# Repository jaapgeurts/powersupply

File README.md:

# Variable power supply

This project is my first attempt at a variable voltage power supply with current limiting.

The power supply can regulate from 0-25v and handle about 3 Amps depending on how well the series pass transistor is heatsinked.

Regulation is not very stable when current limiting kicks in. This requires further analysis.

If you've built and/or improved this project I would like to hear from you.

**Warning**

I make no guarantees towards the correctness or quality of this project.

If you decide to build this project and use this power supply, you do so at your own risk.

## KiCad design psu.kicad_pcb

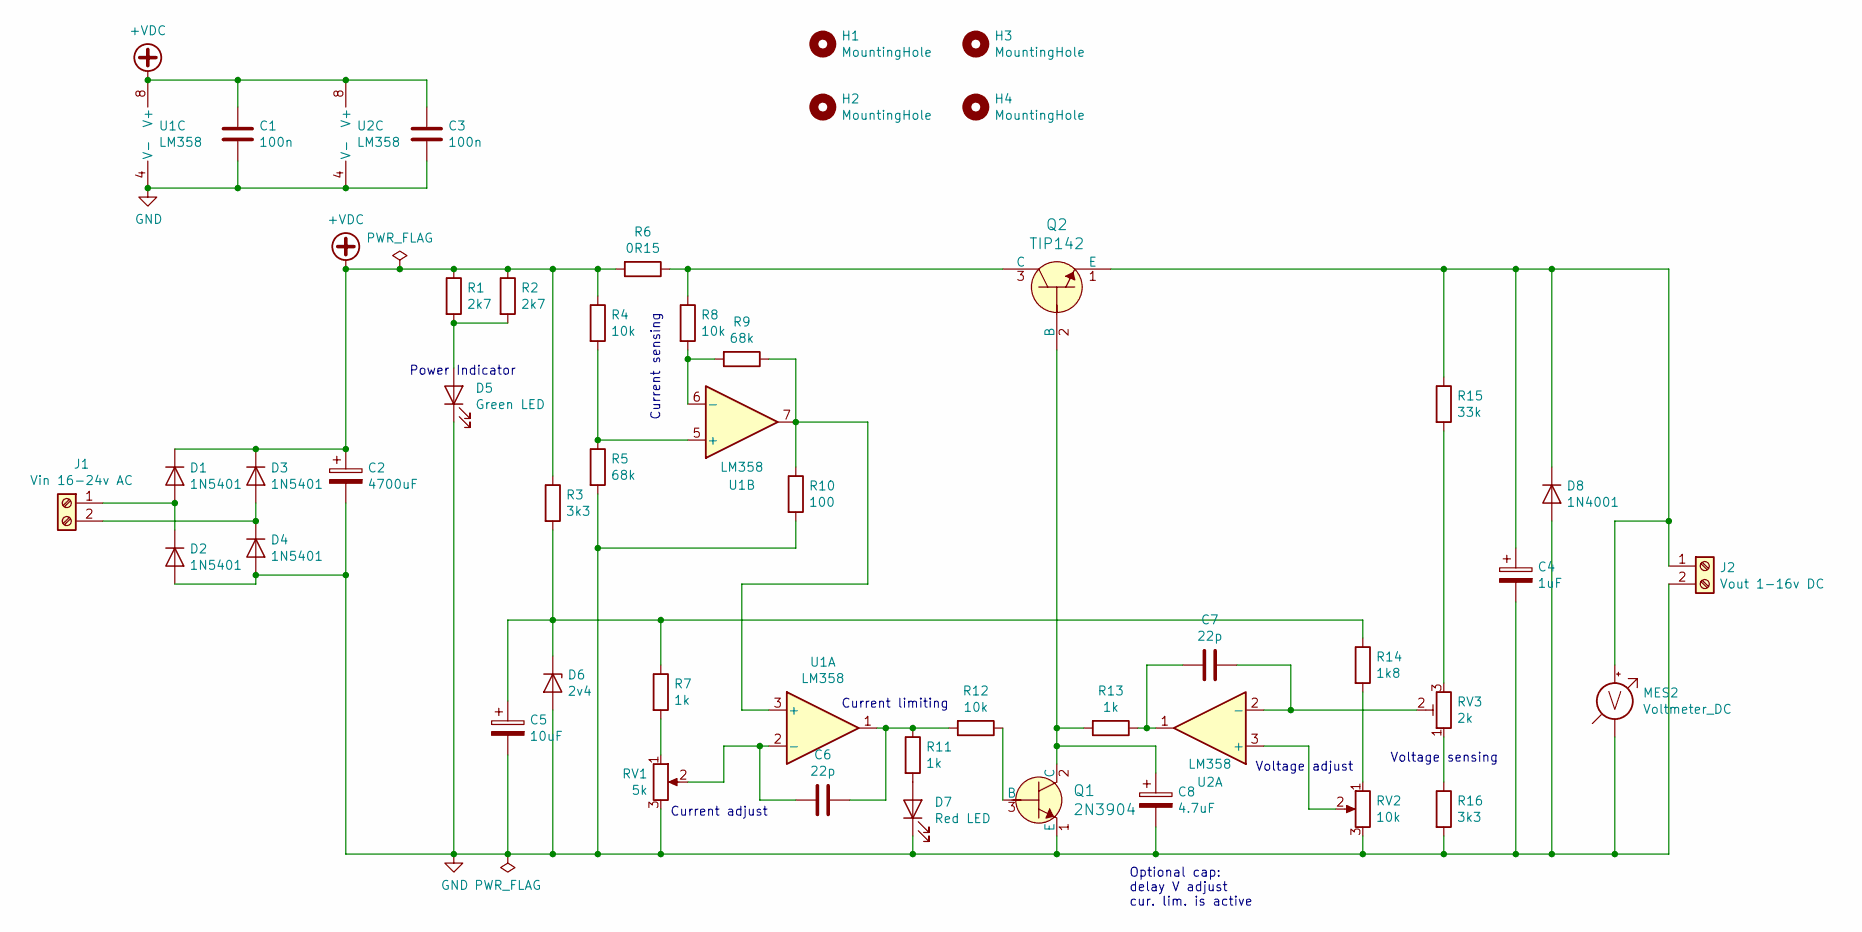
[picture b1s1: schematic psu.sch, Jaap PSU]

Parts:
C1, C3: 100n; C_Disc_D5.1mm_W3.2mm_P5.00mm
C2: 4700uF; CP_Radial_D16.0mm_P7.50mm
C4: 1uF; CP_Radial_D5.0mm_P2.50mm
C5: 10uF; CP_Radial_D5.0mm_P2.50mm
C6, C7: 22p; C_Disc_D5.1mm_W3.2mm_P5.00mm
C8: 4.7uF; CP_Radial_D5.0mm_P2.50mm
D1, D2, D3, D4: 1N5401; D_DO-201AD_P15.24mm_Horizontal
D5: Green LED; PinHeader_1x02_P2.54mm_Vertical
D6: 2v4; D_DO-35_SOD27_P10.16mm_Horizontal
D7: Red LED; PinHeader_1x02_P2.54mm_Vertical
D8: 1N4001; D_DO-41_SOD81_P10.16mm_Horizontal
H1, H2, H3, H4: MountingHole; MountingHole_4.3mm_M4
J1: Vin 16-24v AC; TerminalBlock_Altech_AK300-2_P5.00mm
J2: Vout 1-16v DC; TerminalBlock_Altech_AK300-2_P5.00mm
MES2: Voltmeter_DC; PinHeader_1x02_P2.54mm_Vertical
Q1: 2N3904; TO-92_HandSolder_LongPads; MPN 2N3904; Digi-Key_PN 2N3904CS-ND
Q2: TIP142; PinHeader_1x03_P2.54mm_Vertical; MPN TIP142; Digi-Key_PN 497-2541-5-ND
R1, R2: 2k7; R_Axial_DIN0207_L6.3mm_D2.5mm_P10.16mm_Horizontal
R3, R16: 3k3; R_Axial_DIN0207_L6.3mm_D2.5mm_P10.16mm_Horizontal
R4, R8, R12: 10k; R_Axial_DIN0207_L6.3mm_D2.5mm_P10.16mm_Horizontal
R5, R9: 68k; R_Axial_DIN0207_L6.3mm_D2.5mm_P10.16mm_Horizontal
R6: 0R15; R_Axial_DIN0617_L17.0mm_D6.0mm_P20.32mm_Horizontal
R7, R11, R13: 1k; R_Axial_DIN0207_L6.3mm_D2.5mm_P10.16mm_Horizontal
R10: 100; R_Axial_DIN0207_L6.3mm_D2.5mm_P10.16mm_Horizontal
R14: 1k8; R_Axial_DIN0207_L6.3mm_D2.5mm_P10.16mm_Horizontal
R15: 33k; R_Axial_DIN0207_L6.3mm_D2.5mm_P10.16mm_Horizontal
RV1: 5k; PinHeader_1x03_P2.54mm_Vertical
RV2: 10k; PinHeader_1x03_P2.54mm_Vertical
RV3: 2k; Potentiometer_Runtron_RM-063_Horizontal
U1, U2: LM358; DIP-8_W7.62mm_LongPads

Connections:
+VDC: C1.1, C2.1, C3.1, D1.1 (K), D3.1 (K), R1.1, R2.1, R3.1, R4.1, R6.2, U1.8 (V+), U2.8 (V+)
GND: C1.2, C2.2, C3.2, C4.2, C5.2, C8.2, D2.2 (A), D4.2 (A), D5.1 (K), D6.2 (A), D7.1 (K), D8.2 (A), J2.2, MES2.1 (-), Q1.1 (E), R5.2, R10.2, R16.2, RV1.3, RV2.3, U1.4 (V-), U2.4 (V-)
unnamed: C4.1, D8.1 (K), J2.1, MES2.2 (+), Q2.1 (E), R15.1
unnamed: C5.1, D6.1 (K), R3.2, R7.1, R14.1
unnamed: C6.1, R11.1, R12.2, U1.1
unnamed: C6.2, RV1.2, U1.2 (-)
unnamed: C7.1, RV3.2, U2.2 (-)
unnamed: C7.2, R13.1, U2.1
unnamed: C8.1, Q1.2 (C), Q2.2 (B), R13.2
unnamed: D1.2 (A), D2.1 (K), J1.1
unnamed: D3.2 (A), D4.1 (K), J1.2
unnamed: D5.2 (A), R1.2, R2.2
unnamed: D7.2 (A), R11.2
unnamed: Q1.3 (B), R12.1
unnamed: Q2.3 (C), R6.1, R8.1
unnamed: R4.2, R5.1, U1.5 (+)
unnamed: R7.2, RV1.1
unnamed: R8.2, R9.2, U1.6 (-)
unnamed: R9.1, R10.1, U1.3 (+), U1.7
unnamed: R14.2, RV2.1
unnamed: R15.2, RV3.3
unnamed: R16.1, RV3.1
unnamed: RV2.2, U2.3 (+)

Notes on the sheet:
Optional cap: delay V adjust cur. lim. is active
Current adjust
Voltage adjust
Voltage sensing
Current sensing
Current limiting
Power Indicator

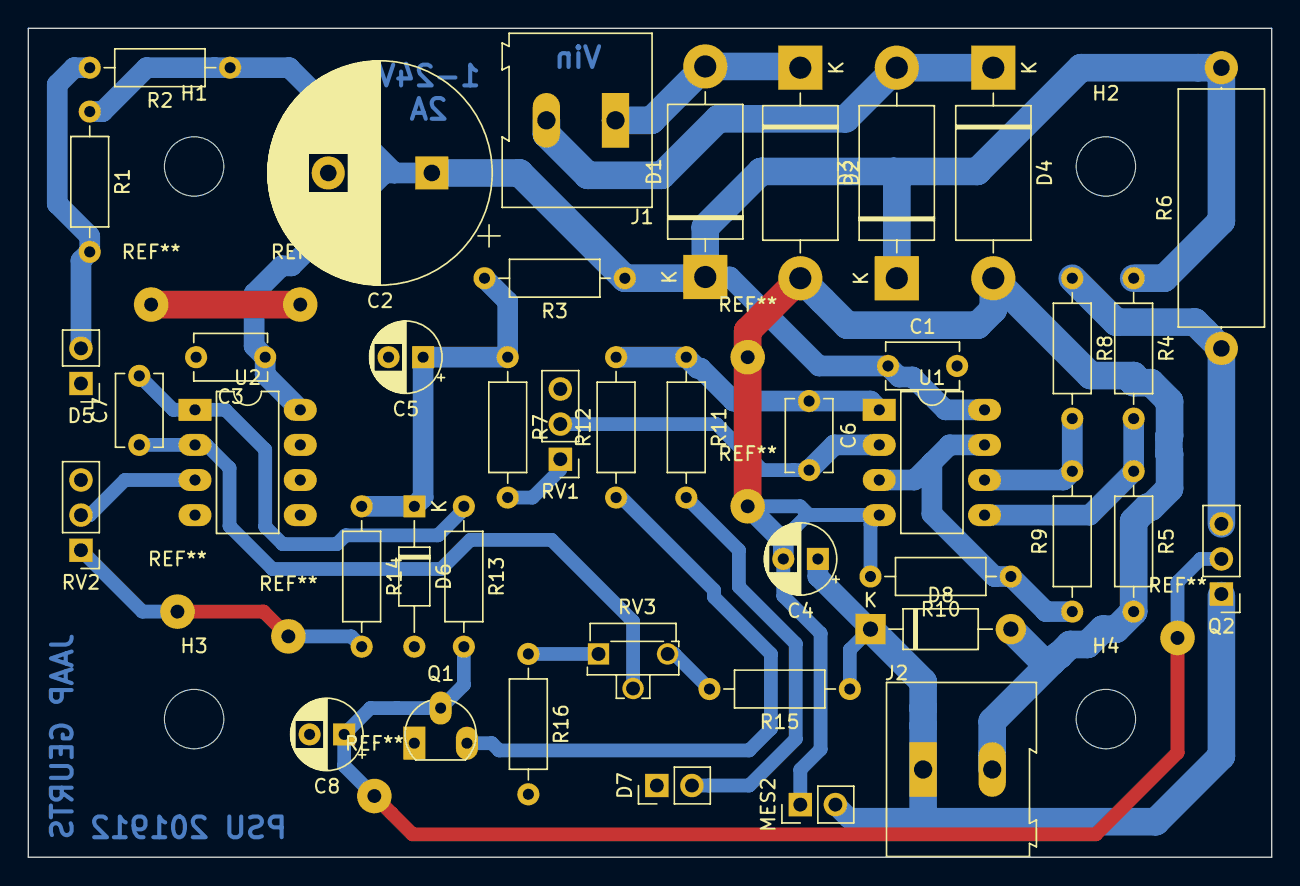
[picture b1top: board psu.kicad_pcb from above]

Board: 2 copper layers, 90.0 x 60.0 mm, 46 parts (0 on the bottom side), 23 nets.

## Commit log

2019-12-04 First working version
2019-12-09 Added falstad simulations
2019-12-11 Circuit Schematic complete
2019-12-16 First etched version
2020-04-06 Added readme and license
